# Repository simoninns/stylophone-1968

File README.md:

# Stylophone-1968
## Overview
This project provides several resources to document, recreate and enhance the original 1968 Dubreq Stylophone.

Note: There have been several versions of the original Stylophone ("New Sound") and a more modern recreation - this project is only for the original 1968 version.

Included in the project are:

* A modern KiCAD schematic for the original Stylophone
* Wiki-based Documentation on the functionality and design of the Stylophone
* Libre-Office spreadsheets demonstrating the maths within the design
* An OpenSCAD recreation of the Stylophone's case (modified for FFF 3D printing).

For more information about any of the above please see [the project wiki](https://github.com/simoninns/stylophone-1968/wiki)

## Author
This project is created, designed and maintained by Simon Inns.

# Licensing
## Source code files - software license (GPLv3)

    This is free software: you can redistribute it and/or modify
    it under the terms of the GNU General Public License as published by
    the Free Software Foundation, either version 3 of the License, or
    (at your option) any later version.
    
    This program is distributed in the hope that it will be useful,
    but WITHOUT ANY WARRANTY; without even the implied warranty of
    MERCHANTABILITY or FITNESS FOR A PARTICULAR PURPOSE.  See the
    GNU General Public License for more details.
    
    You should have received a copy of the GNU General Public License
    along with this program.  If not, see <http://www.gnu.org/licenses/>.

## Non-source-code media - Creative Commons license (Creative Commons BY-SA 4.0)
Please see the following link for details: https://creativecommons.org/licenses/by-sa/4.0/

You are free to:

Share - copy and redistribute the material in any medium or format
Adapt - remix, transform, and build upon the material
for any purpose, even commercially.

This license is acceptable for Free Cultural Works.

The licensor cannot revoke these freedoms as long as you follow the license terms.

Under the following terms:

Attribution - You must give appropriate credit, provide a link to the license, and indicate if changes were made. You may do so in any reasonable manner, but not in any way that suggests the licensor endorses you or your use.

ShareAlike - If you remix, transform, or build upon the material, you must distribute your contributions under the same license as the original.

No additional restrictions - You may not apply legal terms or technological measures that legally restrict others from doing anything the license permits.

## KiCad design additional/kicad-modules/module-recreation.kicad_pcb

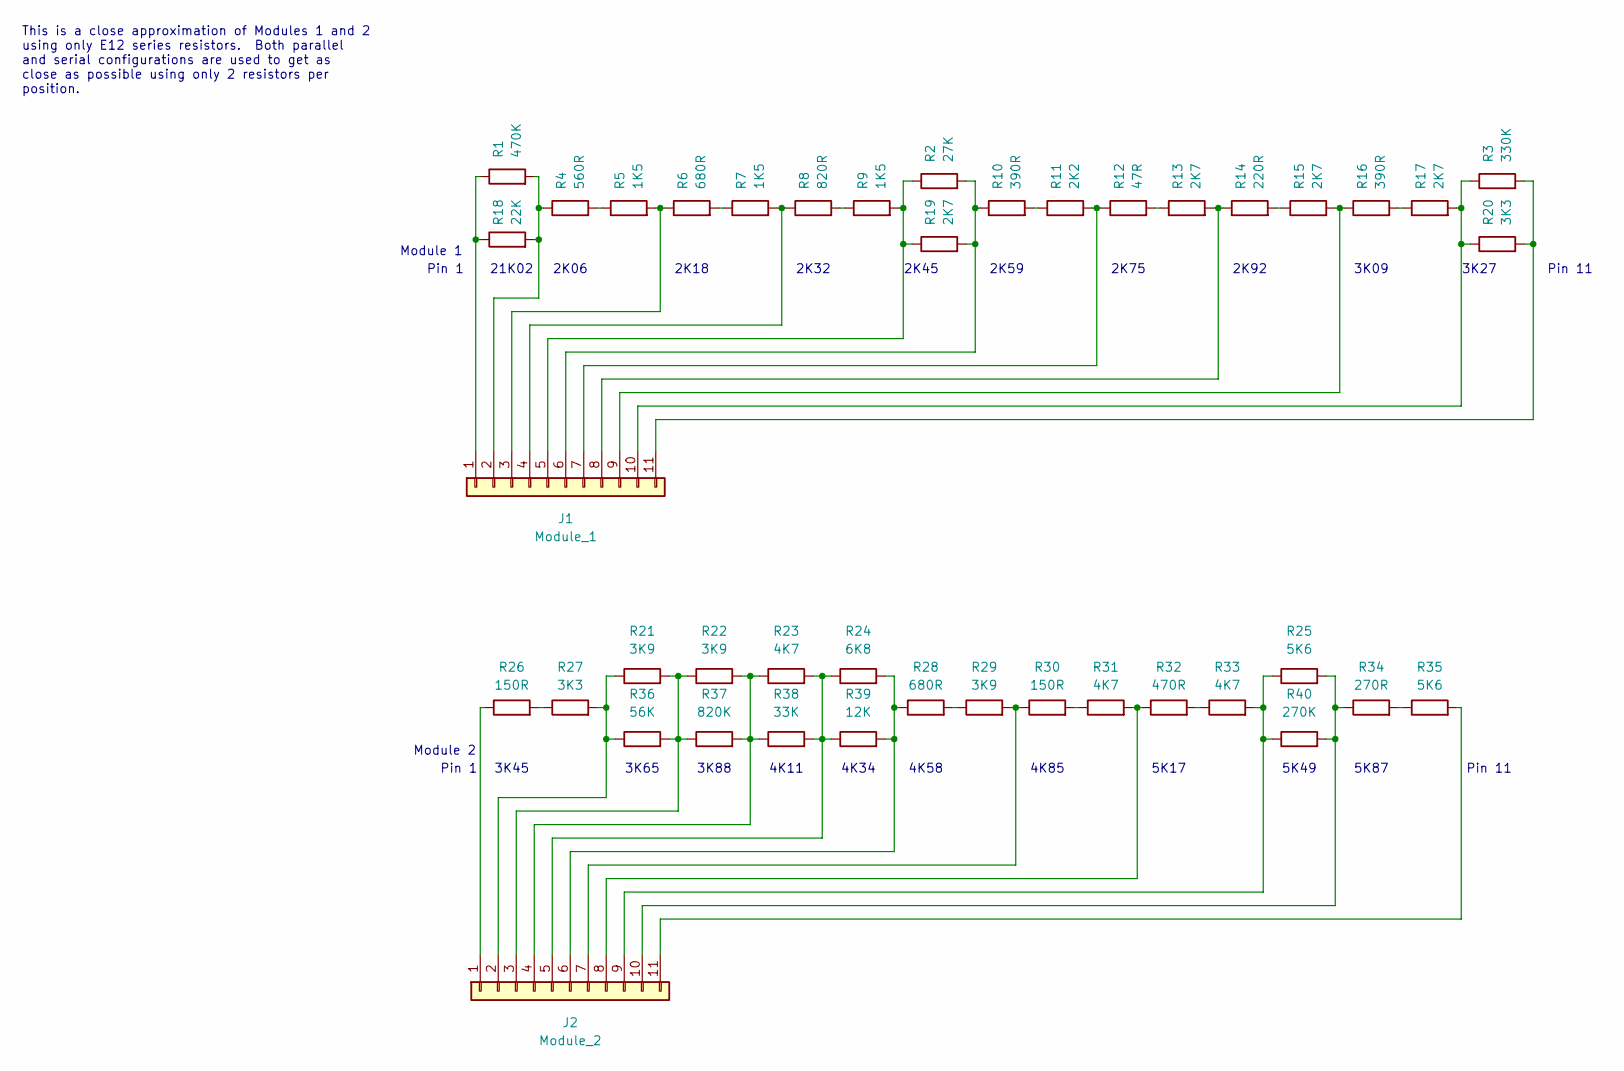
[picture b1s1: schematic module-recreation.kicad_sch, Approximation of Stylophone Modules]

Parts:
J1: Module_1; PinHeader_1x11_P2.54mm_Horizontal
J2: Module_2; PinHeader_1x11_P2.54mm_Horizontal
R1: 470K; R_0805_2012Metric
R2: 27K; R_0805_2012Metric
R3: 330K; R_0805_2012Metric
R4: 560R; R_0805_2012Metric
R5, R7, R9: 1K5; R_0805_2012Metric
R6, R28: 680R; R_0805_2012Metric
R8: 820R; R_0805_2012Metric
R10, R16: 390R; R_0805_2012Metric
R11: 2K2; R_0805_2012Metric
R12: 47R; R_0805_2012Metric
R13, R15, R17, R19: 2K7; R_0805_2012Metric
R14: 220R; R_0805_2012Metric
R18: 22K; R_0805_2012Metric
R20, R27: 3K3; R_0805_2012Metric
R21, R22, R29: 3K9; R_0805_2012Metric
R23, R31, R33: 4K7; R_0805_2012Metric
R24: 6K8; R_0805_2012Metric
R25, R35: 5K6; R_0805_2012Metric
R26, R30: 150R; R_0805_2012Metric
R32: 470R; R_0805_2012Metric
R34: 270R; R_0805_2012Metric
R36: 56K; R_0805_2012Metric
R37: 820K; R_0805_2012Metric
R38: 33K; R_0805_2012Metric
R39: 12K; R_0805_2012Metric
R40: 270K; R_0805_2012Metric

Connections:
unnamed: J1.1, R1.1, R18.1
unnamed: J1.2, R1.2, R4.1, R18.2
unnamed: J1.3, R5.2, R6.1
unnamed: J1.4, R7.2, R8.1
unnamed: J1.5, R2.1, R9.2, R19.1
unnamed: J1.6, R2.2, R10.1, R19.2
unnamed: J1.7, R11.2, R12.1
unnamed: J1.8, R13.2, R14.1
unnamed: J1.9, R15.2, R16.1
unnamed: J1.10, R3.1, R17.2, R20.1
unnamed: J1.11, R3.2, R20.2
unnamed: J2.1, R26.1
unnamed: J2.2, R21.1, R27.2, R36.1
unnamed: J2.3, R21.2, R22.1, R36.2, R37.1
unnamed: J2.4, R22.2, R23.1, R37.2, R38.1
unnamed: J2.5, R23.2, R24.1, R38.2, R39.1
unnamed: J2.6, R24.2, R28.1, R39.2
unnamed: J2.7, R29.2, R30.1
unnamed: J2.8, R31.2, R32.1
unnamed: J2.9, R25.1, R33.2, R40.1
unnamed: J2.10, R25.2, R34.1, R40.2
unnamed: J2.11, R35.2
unnamed: R4.2, R5.1
unnamed: R6.2, R7.1
unnamed: R8.2, R9.1
unnamed: R10.2, R11.1
unnamed: R12.2, R13.1
unnamed: R14.2, R15.1
unnamed: R16.2, R17.1
unnamed: R26.2, R27.1
unnamed: R28.2, R29.1
unnamed: R30.2, R31.1
unnamed: R32.2, R33.1
unnamed: R34.2, R35.1

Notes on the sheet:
2K32
2K75
4K85
5K49
2K06
This is a close approximation of Modules 1 and 2 using only E12 series resistors. Both parallel and serial configurations are used to get as close as possible using only 2 resistors per position.
4K34
3K27
3K45
Pin 11
2K45
2K92
3K65
Pin 1
Module 1
2K59
3K88
Module 2
3K09
2K18
5K87
4K11
4K58
5K17
21K02

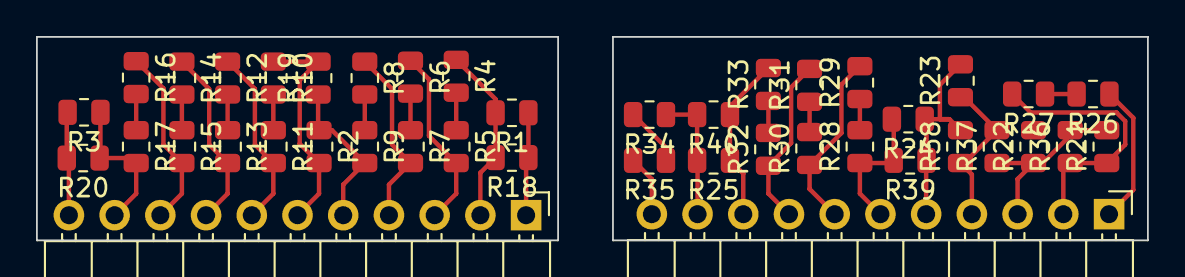
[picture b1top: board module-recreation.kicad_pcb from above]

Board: 2 copper layers, 61.7 x 11.3 mm, 42 parts (0 on the bottom side), 34 nets.

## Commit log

2023-01-15 First push to public repo from private gitlab
2023-01-15 Added wiki link to readme
2023-01-15 Added an example of how to rebuild the modules using E12 resistors
2023-01-15 Added a rough PCB design to the modules
2023-01-16 Changed diode value and improved oscillator tuning schematic
2023-01-31 Fixed value of R31 due to issue #1

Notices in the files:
additional/kicad-modules/module-recreation.kicad_sch:
(c) 2023 Simon Inns
License: Attribution-ShareAlike 4.0 International (CC BY-SA 4.0)
